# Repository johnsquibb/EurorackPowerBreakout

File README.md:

# EurorackPowerBreakout
Eurorack 10-pin power breakout, designed to fit a standard breadboard.
[Learn More](http://johnsquibb.com/articles/electronics/eurorack-power-breakout-board.html)

## Features
- Designed for use with 10 pin keyed horizontal box header.
- Fits standard breadboard with attached bus bars having 0.1" lead spacing.
- +/-12V with button power on/off (optional)
- LED indicators (optional).
- 10uF local power bypass (optional) 

## Usage
The breakout board is designed to be placed on the left-hand or right-hand side of a standard breadboard with 0.1" lead spacing. For the left-hand orientation, the -12V connection will be on the top power bus rail, and +12V on the bottom. This coincides with the power pins of a left-hand orientation of a TL074 op amp IC package that I frequently use (pins 4 and 11). See [image](./image/eurorackPower10pin_breadboard.jpg) for a visual reference.

The LEDs are optional, and can be omitted and/or replaced with extra header pins. I use the convention of red for +12V and yellow for -12V. I use a minimum of 1k ohm resistors for LEDs, but higher values may be used to reduce the brightness.

The DPDT power button is optional and can be replaced with header pins and jumpers, or omitted entirely. If omitted, pins 2 and 3 must be bridged for `DPDT_A` and `DPDT_B` connections (Note: pin 1 is identified by square pad).

The power bypass capacitors are optional and can be omitted without modification to the circuit. I recommend using at least 50V capacitors for +/-12V Eurorack power connections. I've linked my preferred caps below in the Bill of Materials, as they are short and less susceptible to bending when handling the board.

## Bill of Materials
All through-hole components.

Here's a list of some of the specialized parts:

- [10 PIN BOX HEADER CONNECTOR 2.54MM RIGHT ANGLE](https://www.taydaelectronics.com/10-pin-box-header-connector-2-54mm-right-angle.html)
- [DPDT 8x8mm](https://www.taydaelectronics.com/push-button-switch-latching-on-off-dpdt-0-5a-50vdc-8x8mm.html)
- [3mm LED (yellow)](https://www.taydaelectronics.com/led-3mm-yellow.html)
- [3mm LED (red)](https://www.taydaelectronics.com/led-3mm-red.html)
- [10uF Electroylitic Capacitors](https://www.digikey.com/product-detail/en/nichicon/UMT1H100MDD/493-15562-ND/2598786)

See the [interactive BOM](./bom/ibom.html) document for interactive visual guide.

## License
Schematic and PCB designs by John Squibb are licensed under MIT (see LICENSE).

All other software dependencies are the copyright of their respective owners.

See KiCad and InteractiveHtmlBom projects for their software licenses:

* [https://github.com/KiCad](https://github.com/KiCad)

* [https://github.com/openscopeproject/InteractiveHtmlBom](https://github.com/openscopeproject/InteractiveHtmlBom)

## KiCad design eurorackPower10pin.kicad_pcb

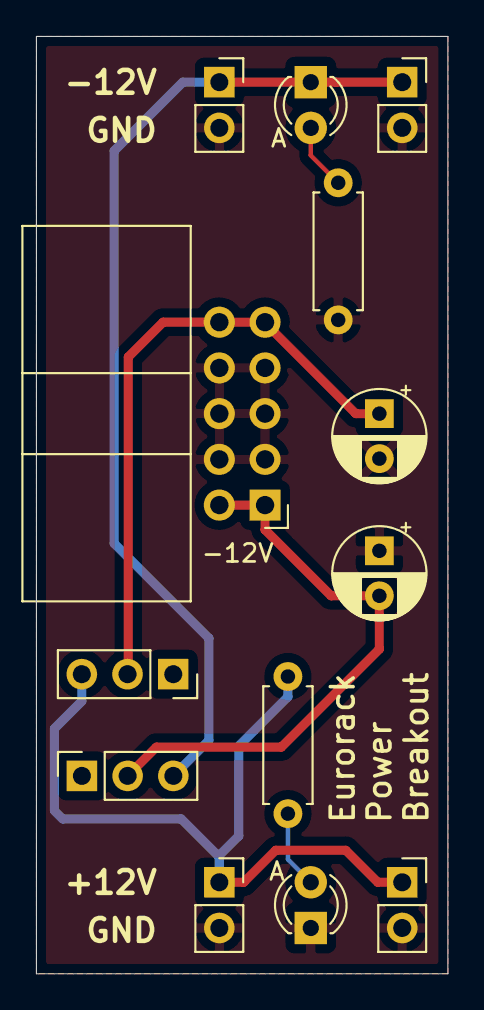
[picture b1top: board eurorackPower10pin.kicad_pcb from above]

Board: 2 copper layers, 22.9 x 52.1 mm, 13 parts (0 on the bottom side), 7 nets.

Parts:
C1, C2: 10uF; CP_Radial_D5.0mm_P2.50mm
D1, D2: LED; LED_D3.0mm
J1: Eurorack Power; IDC-Header_2x05_P2.54mm_Horizontal
J2: DPDT_A; PinSocket_1x03_P2.54mm_Vertical
J3: RailPinTop A; PinSocket_1x02_P2.54mm_Vertical
J4: DPDT_B; PinSocket_1x03_P2.54mm_Vertical
J5: RailPinBot A; PinSocket_1x02_P2.54mm_Vertical
J6: RailPinTop B; PinSocket_1x02_P2.54mm_Vertical
J7: RailPinBot B; PinSocket_1x02_P2.54mm_Vertical
R1, R2: 1K; R_Axial_DIN0207_L6.3mm_D2.5mm_P7.62mm_Horizontal

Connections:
+12V: C1.1, J1.9, J1.10, J4.2
-12V: C2.2, J1.1, J1.2, J2.2
/+12VRail: J4.3, J5.1, J7.1, R1.1
/-12Rail: D1.1, J2.3, J3.1, J6.1
GND: C1.2, C2.1, D2.1, J1.3, J1.4, J1.5, J1.6, J1.7, J1.8, J3.2, J5.2, J6.2, J7.2, R2.2
unnamed: D1.2, R2.1
unnamed: D2.2, R1.2

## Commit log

2020-06-20 Create LICENSE
2020-06-20 Adding design files, updating README
2020-06-20 Moving Gerber files into subdirectory to reduce clutter
2020-06-20 Replacing images with scaled and minified versions
2020-06-20 Moving images to subdirectory, updated README refs
2020-06-20 Fixing awkward sentence
    Clarifying the dimensions of breadboard.
2020-06-20 Update README.md
    Added link to website with article containing additional details.
2023-10-04 Update README.md
    fixed broken link to web page reference
2023-10-04 Update README.md
    Making link readable
